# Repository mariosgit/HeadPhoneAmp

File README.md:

# HeadPhoneAmp

New plan... Make my own HP Amp.

##### Requirements:

* EQ - I dont have many HP's which I don't want to EQ, they all need a little something.
* Lipo Powered !
* Line In

##### Goodies

* More Inputs (in that order)
   * USB (Teensy4 can also control DSP, Bluetooth, 16bit is ok for playback)
   * BT (just plug in a module CSR8635?)
   * WLAN (Radio, Subsonic and Ampache protocols for nextcloud music) cry for ESP32 (rabbithole! [bt a2dp](https://github.com/pschatzmann/ESP32-A2DP) [iradio](https://github.com/Edzelf/ESP32Radio-V2) [streem gedoehns](https://github.com/sle118/squeezelite-esp32) )
   * SPDIF (not really on a HP amp)
   * Analog++ Phono MM input with RIAA https://sound-au.com/project06.htm 
* Second output ? With it's own EQ and Volume ?
* NuTube or Simulation of a little distortion. Maybe other effects ?
* MP3 player - there is one for the teensy. Would need SDCard or so, How to copy files ? Just swap the card ? The Cardhold would obscure the VUSB hack !
* ~~Radio streaming.. WLAN hasl...~~

# Status

* Theory is somewhat more defined in my head.
* Started to build some blocks
    * TPA6120 module - Made my own, running with only single 5V - to be tested.
    * DSP - I have a freeDSP-SMD-B to experiment with
    * NuTube ? I have a NuTube HP Amp which is'nt great but could be recycled into something usefull - not so available !

# Tested so far...

## HPAmp Design

TPA6120A2 it's big (there is a QFN version) and a TPS65135 power converter as per datasheet.

After some mangling, it performs well, no noise and quite some punch.

##### Bugs v0.1

* Wrong TPA6120 footprint :-(

##### Bugs v0.2 / Eval

* ~~Oszilation on left output 12MHz ?? goes awai when osziloscoping the input line !?~~ Gone after adding C5, C4 2.2u from se reste kiste.
* There is some noise and DC offset of 500mV, as is in the PRC breakout of this amp. Added 1k @ inputs to ground -> silence, no/minimal Vout offset.
* input resistors to ground ? **YES** !
    * 47k was noisy
    * 1k is ok, depends on input ? consider previous stage power output !
* 10uF caps footprint could be larger / dual 1206?
* On/Off clics ? Not too bad.
* Add TestPoints for L/R inputs
* Add LEDs for +-5V ?
* TestPoint and pullup for EN pin.
* More ground pads.
* Does not work with small BAT/Charger? Toggles on/off

## Power Block Design

* Use Adafruit PowerThing ?
    * Added charge pump for 10V as in the DS
* How to get the teensy integrated, would need to patch into VUSB -> PowerBlock -> 5V back to the Teensy ?
    * Cut trace in the back, solder some wire to VUSB ? Or use pogopins ? Not nice.
* Noise ??? Will see... yes 200mVpp @ 65kHz, audible when directly driving a 16ohm speaker

* Cap Mult for analog voltage, or just a regulator ? [SIM](https://www.falstad.com/circuit/circuitjs.html?ctz=CQAgjCAMB0l3BWcDoBYDsAmdA2dBOdMMADhzEnxAQiVQGZqBTAWmICgAnEbTHkkjyzgwfSMkjsAxuHx8wuWX0ypxa2PEiY+6aPjAMi6dJAOpMCdCDaTuOVOEVgc4hTig9McdgDdr+d20HFgCRMXBweAiqdQR2AHN-QJUk-kE1BKFlASyQekgHDIB3HkhBYmVhCvB2ABclcFQHMDkwvIiWGDl9fEh0BHwEchILMWgcQYQtS3xzPonmuBAAEyYAMwBDAFcAG1r2EpbswV40qAOGt0um88OXR3cjxsKL+weQN+qwV+bRd+rJAAHPIIeQ3eigniqdrFEFghwQ+R-SQlRFtU4Ai5olTibE5FFws6nTD4i4hdwseh8cltAk06qfZEXJ6oE7CVnnGRPSnyVoc9SaLR8EjQYxgBAIVT0QgUVA4QQ2TIs8qtN4ZbinDmnHkecVAwk6tEcxiwo1svj8smhHVsClU24NHXa+3fErOvhonW2azOawu1pemqHVoklXKaGSAD27XSIAAHiQTGAAEYfKAaUy6njWdD0djRsCMWMJ-J-eh6HDkBACPDEaX0dwweAQFvZli4fPgIseONSQt-CjpiDyCIwJBRqEgYt90zydQQRitsfnejlEAAMQgAs0W4zFAgbBAAGENoCNlIAJa1DYAOykTHYq48m6z+59IAASkwAM4X7-Xu8HyAA)

##### Results v0.1

* C6 can be much larger according to DS. Available up to 220uF.
* Has no BAT protection ? The testbat emptied down to 2V ! Just clarify.
* Make charge Amps quick changeable with a PHT resistor ?
* Could add a PG PowerGood LED, this shows when device is connected to some power source
* Check 10V load ❗
* Add option for higher voltage as in the GP??94 controller ?

##### Bugs v0.1

* ! Q1 (low bat indicator) is **wrong** MMUN2133LT1G it's BEC(123) - just switched to the "BEC" symbol. ✅
* C5 (+10V) was connected to ground, should be between +10 and +5V, works anyway ✅
* Can it provide 50V using a longer charge pump ?

# Next up ?

## NuTube

* Create own board 
    * Bias voltage driven by OpAmp ! Input a single Pot or CV
    * With ADC ? as a FX loopback ?
* Loop back Nutube to DSP ? With an extra ADC or CODEC ? Ad

## VFD/OLED

* Make board for MN12832 ?
    * Can I borrow voltage from the power block ? Add more charge pumps..

## Teensy/ESP32/STM32 + DSP

* Can the teensy be slave i2s ??? Otherwise it would need an extra SRC.
    There is a slave i2s out... Will it work with usb, does it need to be 44100kHz ?
    ```
    AudioInputUSB            usb1;
    AudioOutputI2Sslave      i2sslave1;
    AudioConnection          patchCord1(usb1, 0, i2sslave1, 0);
    AudioConnection          patchCord2(usb1, 1, i2sslave1, 1);
    ```
    ```File > Examples > Audio > HardwareTesting > WM8731MikroSine```
    *Notes: Slave mode I2S should not used in the same project as ADC, DAC and PWM signals. Differences in timing between the I2S device and Teensy's clock can cause occasional audio glitches when I2S slave mode is used together with other input or output objects based on Teensy's timing. ...Only one I2S input and one I2S output object may be used. Master and slave modes may not be mixed (both must be of the same type).*
    Mhm wanted to use the internal DAC for NuTube bias...
* Test I2S slave (with DSP)
* Test internal DAC for NuTube

## BT Audio

* Ahh just another SRC needed ??? Or switch them between Teensy and BT ? And SPDif ?
* Make a SPDIF/BT/USB I2S Switch + SRC  block design. it's all there.

## SRC Board

Because PRC boards are somewhat lacking...

* Jumpers/DIP-Switches for config !

## ADC Board ? 

For more channels ? or FX loops
* PCM1808 1.2Eur - 99db somewhat outdated, TI says try the PCM1822 ! ~3 Eur

## Analog mess

### BBE

### uPC1892

# Log

| What | Time | Cost || What | Time | Cost |
|---|---|---|---|---|---|---|
| Make Power PCB | 1d | | | Test,Fix Power PCB | 1d | |
|  Make HPBooster PCB | 1d | | | | | |
| both mat+pcb | | 50 + 30 | | |

# Refs

Used some Symbols... https://github.com/wykys/klib 

Ti's [I2C expander collection](https://www.ti.com/interface/i2c/general-purpose-ios-gpios/overview.html?keyMatch=i/o%20expander&tisearch=search-everything)

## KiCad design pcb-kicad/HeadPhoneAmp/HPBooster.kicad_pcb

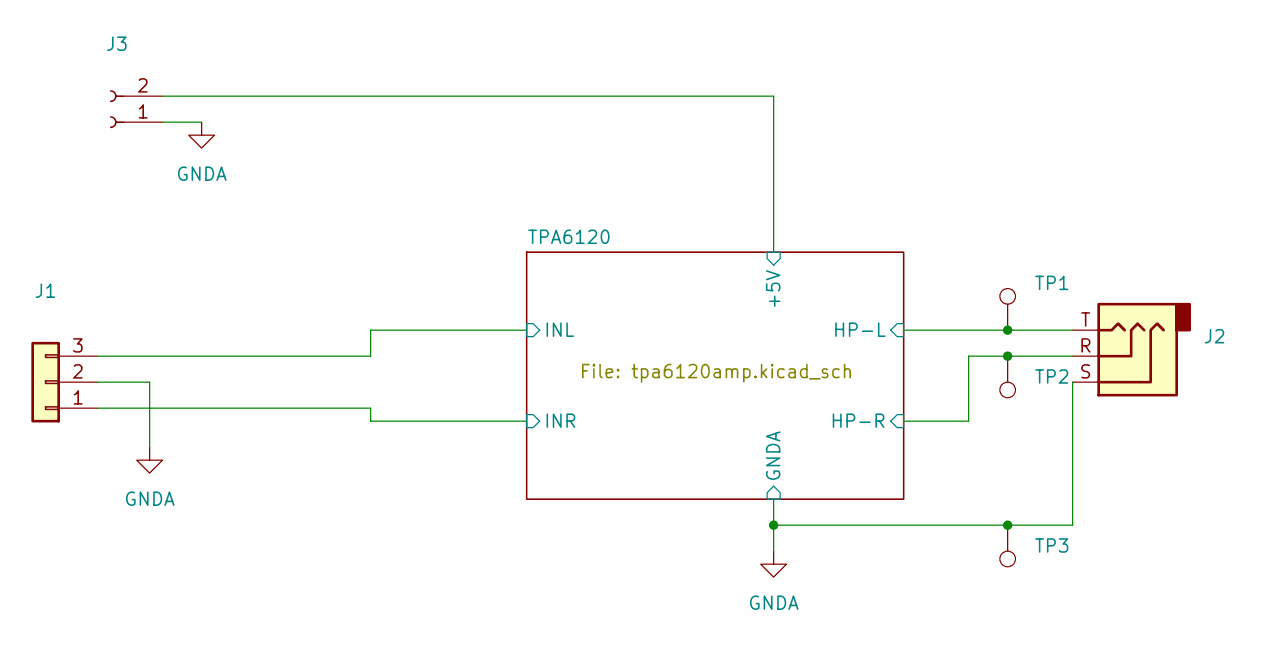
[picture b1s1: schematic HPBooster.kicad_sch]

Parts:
J1: JST_EH_B3B-EH-A_1x03_P2.50mm_Vertical
J2: Jack_3.5mm_CUI_SJ-3523-SMT_Horizontal
J3: PinHeader_1x02_P2.54mm_Vertical
TP1, TP2, TP3: TestPoint_Loop_D1.80mm_Drill1.0mm_Beaded

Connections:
+5V: J3.2; also elsewhere on the board
/TPA6120/HP-L: J2.T, TP1.1; also elsewhere on the board
/TPA6120/HP-R: J2.R, TP2.1; also elsewhere on the board
/TPA6120/INL: J1.3; also elsewhere on the board
/TPA6120/INR: J1.1; also elsewhere on the board
GNDA: J1.2, J2.S, J3.1, TP3.1; also elsewhere on the board

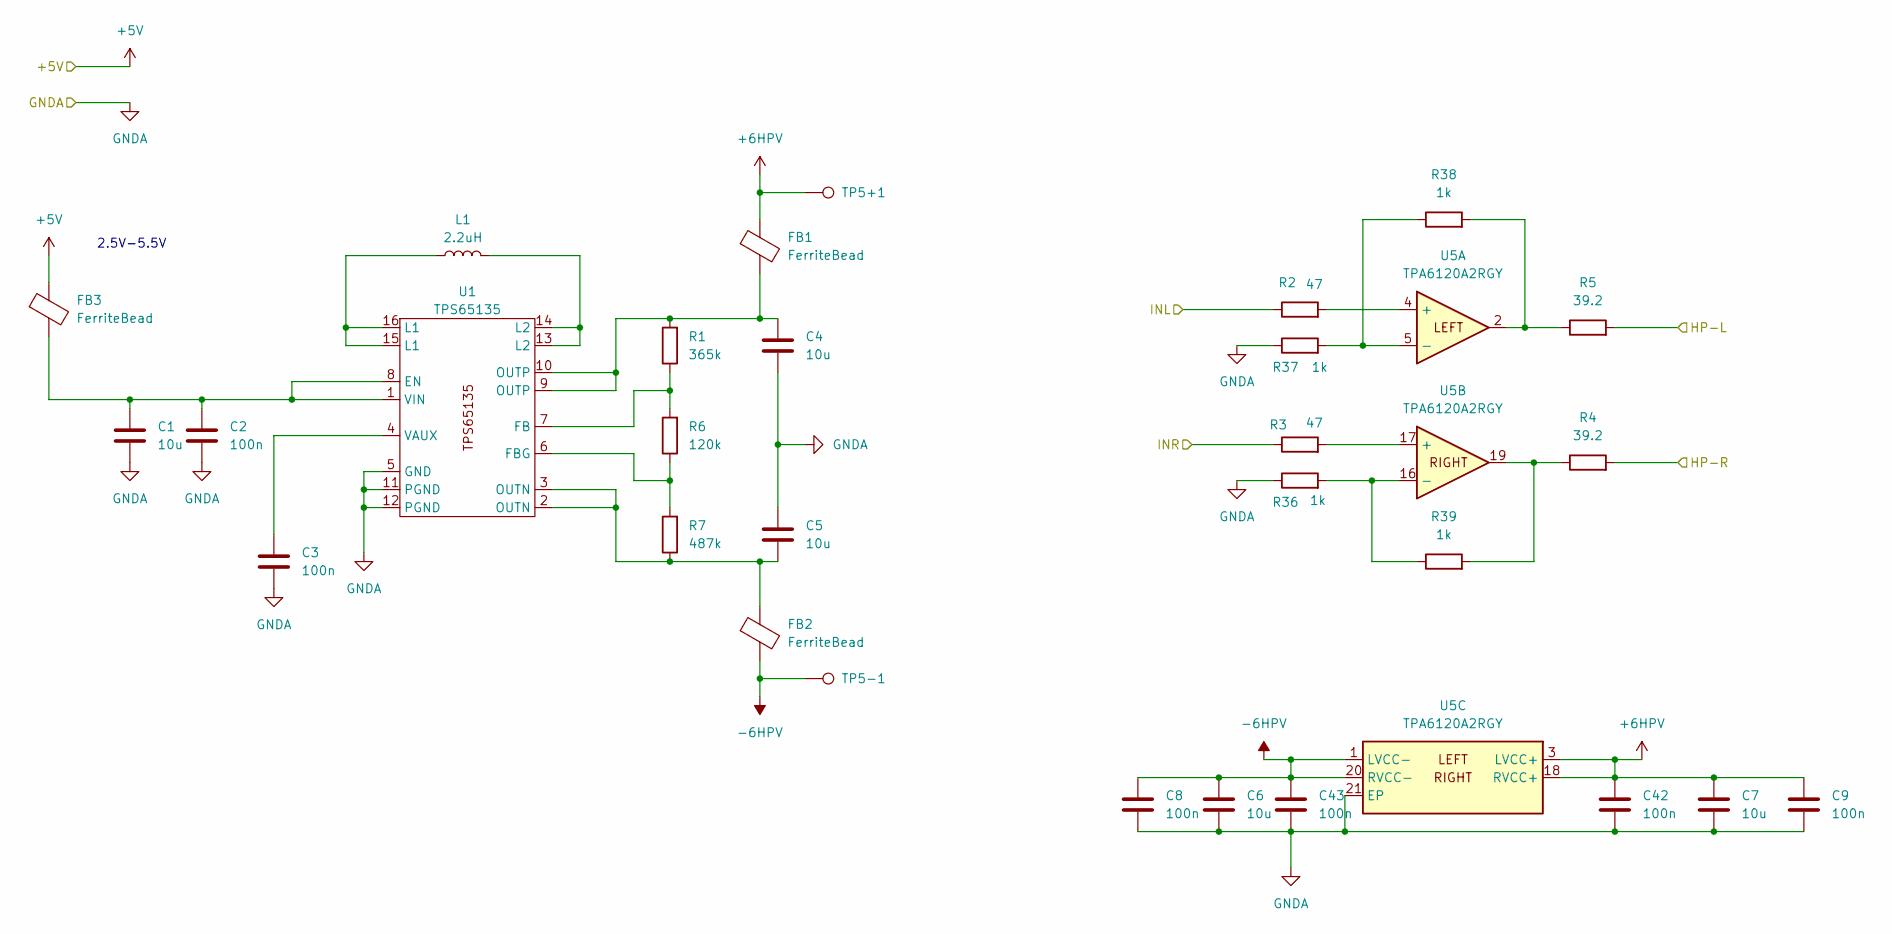
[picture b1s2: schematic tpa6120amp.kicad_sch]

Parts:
C1, C4, C5, C6, C7: 10u; C_0603_1608Metric_Pad1.08x0.95mm_HandSolder
C2, C3, C8, C9, C42, C43: 100n; C_0603_1608Metric_Pad1.08x0.95mm_HandSolder
FB1, FB2, FB3: FerriteBead; L_0603_1608Metric_Pad1.05x0.95mm_HandSolder
L1: 2.2uH; L_1812_4532Metric_Pad1.30x3.40mm_HandSolder
R1: 365k; R_0603_1608Metric_Pad0.98x0.95mm_HandSolder
R2, R3: 47; R_0603_1608Metric_Pad0.98x0.95mm_HandSolder
R4, R5: 39.2; R_2512_6332Metric_Pad1.40x3.35mm_HandSolder
R6: 120k; R_0603_1608Metric_Pad0.98x0.95mm_HandSolder
R7: 487k; R_0603_1608Metric_Pad0.98x0.95mm_HandSolder
R36, R37, R38, R39: 1k; R_0603_1608Metric_Pad0.98x0.95mm_HandSolder
TP5+1, TP5-1: TestPoint_Pad_2.0x2.0mm
U1: TPS65135; WQFN-16-1EP_3x3mm_P0.5mm_LongPad_ThermalVia
U5: TPA6120A2RGY; SOP-20_7.5x12.8mm_P1.27mm

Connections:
+5V: FB3.1; also elsewhere on the board
+6HPV: C7.1, C9.1, C42.1, FB1.1, TP5+1.1, U5.3 (LVCC+), U5.18 (RVCC+)
-6HPV: C6.1, C8.1, C43.1, FB2.2, TP5-1.1, U5.1 (LVCC-), U5.20 (RVCC-)
/TPA6120/HP-L: R5.2; also elsewhere on the board
/TPA6120/HP-R: R4.2; also elsewhere on the board
/TPA6120/INL: R2.1; also elsewhere on the board
/TPA6120/INR: R3.1; also elsewhere on the board
GNDA: C1.2, C2.2, C3.2, C4.2, C5.1, C6.2, C7.2, C8.2, C9.2, C42.2, C43.2, R36.1, R37.1, U1.5 (GND), U1.11 (PGND), U1.12 (PGND), U5.21 (EP); also elsewhere on the board
unnamed: C4.1, FB1.2, R1.2, U1.9 (OUTP), U1.10 (OUTP)
unnamed: C5.2, FB2.1, R7.1, U1.2 (OUTN), U1.3 (OUTN)
unnamed: L1.1, U1.15 (L1), U1.16 (L1)
unnamed: L1.2, U1.13 (L2), U1.14 (L2)
unnamed: R5.1, R38.2, U5.2
unnamed: R4.1, R39.2, U5.19
unnamed: C1.1, C2.1, FB3.2, U1.1 (VIN), U1.8 (EN)
unnamed: R1.1, R6.2, U1.7 (FB)
unnamed: R6.1, R7.2, U1.6 (FBG)
unnamed: C3.1, U1.4 (VAUX)
unnamed: R2.2, U5.4 (+)
unnamed: R37.2, R38.1, U5.5 (-)
unnamed: R3.2, U5.17 (+)
unnamed: R36.2, R39.1, U5.16 (-)

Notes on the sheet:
2.5V-5.5V

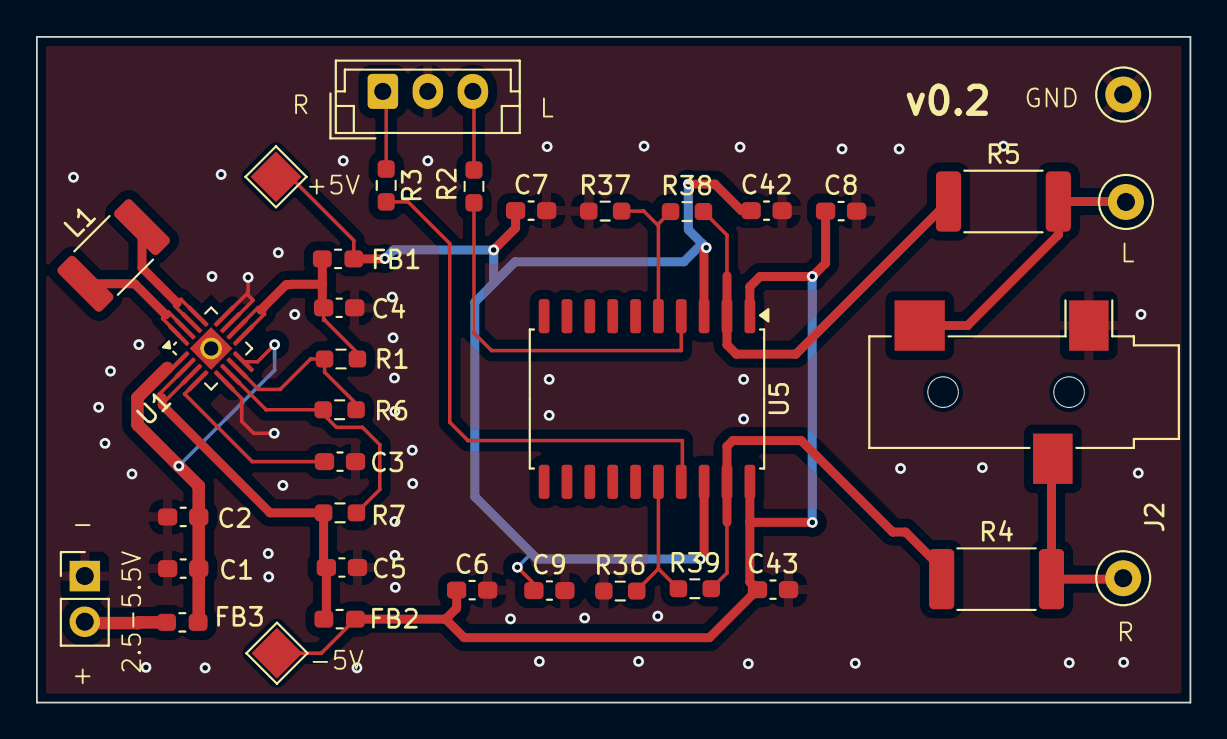
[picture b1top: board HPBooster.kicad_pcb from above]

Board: 2 copper layers, 64.1 x 37.0 mm, 36 parts (0 on the bottom side), 22 nets.

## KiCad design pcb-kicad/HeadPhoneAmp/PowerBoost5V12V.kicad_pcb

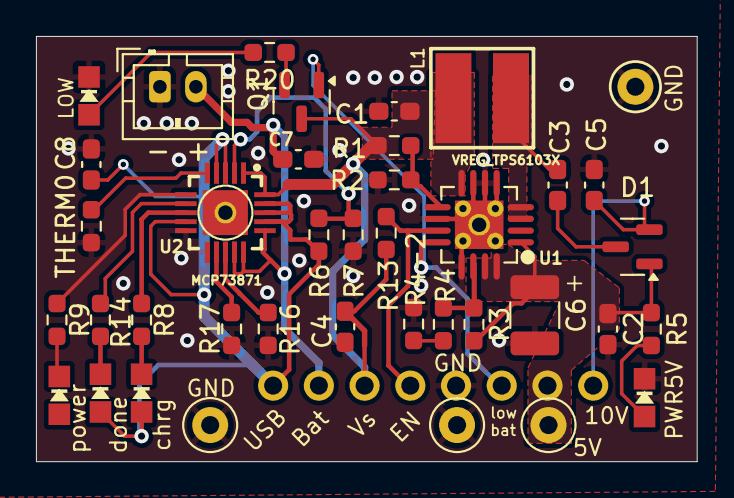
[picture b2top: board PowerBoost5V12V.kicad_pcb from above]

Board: 2 copper layers, 36.7 x 23.6 mm, 41 parts (0 on the bottom side), 26 nets.

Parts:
B1: JST_PH_B2B-PH-K_1x02_P2.00mm_Vertical
C1, C2, C5, C7, C8: 2.2u; C_0603_1608Metric_Pad1.08x0.95mm_HandSolder
C3, C4: 100n; C_0603_1608Metric_Pad1.08x0.95mm_HandSolder
C6: 22u; C_1210_3225Metric_Pad1.33x2.70mm_HandSolder
CHRG/LBO0: CHIPLED_0805_NOOUTLINE
D1: BAT54S; SOT-23
DONE0: CHIPLED_0805_NOOUTLINE
JP2: 1X08_ROUND
L1: 6.8uH 2A; INDUCTOR_5X5MM_TDK_VLC5045
LED1, LED2: CHIPLED_0805_NOOUTLINE
LEDPG1: PG; CHIPLED_0805_NOOUTLINE
Q1: Q_PNP_BEC_BRT; SOT-23
R1, R3: 1.87M; R_0603_1608Metric_Pad0.98x0.95mm_HandSolder
R2: 340k; R_0603_1608Metric_Pad0.98x0.95mm_HandSolder
R4, R4-2, R7, R13, R17: 100k; R_0603_1608Metric_Pad0.98x0.95mm_HandSolder
R5, R8, R9, R14, R16, R20: 1k; R_0603_1608Metric_Pad0.98x0.95mm_HandSolder
R6: 270k; R_0603_1608Metric_Pad0.98x0.95mm_HandSolder
THERM0: 15k; R_0603_1608Metric_Pad0.98x0.95mm_HandSolder
TP1: TestPoint_Keystone_5000-5004_Miniature
TP2, TP3, TP4, TP5: TestPoint_Loop_D1.80mm_Drill1.0mm_Beaded
U1: VREG_TPS6103X; PVQFN-16
U2: MCP73871; QFN20_4MM

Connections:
5.0V: C2.1, C6.1, D1.1 (A), JP2.7, R3.2, R5.1, TP2.1, U1.1 (VOUT), U1.15 (VOUT), U1.16 (VOUT)
+10V: C5.1, D1.2 (K), JP2.8
/ENABLE: JP2.4, R13.2, U1.11 (EN)
/LBO: JP2.6, Q1.1 (B), U1.12 (LBO)
GND: B1.1 (-), C1.2, C2.2, C4.2, C5.2, C6.2, C7.2, C8.2, JP2.5, LED1.C, LED2.C, R2.1, R4-2.1, R7.2, R16.1, R17.1, THERM0.1, TP1.1, TP3.1, TP4.1, TP5.1, U1.5 (PGND), U1.6 (PGND), U1.7 (PGND), U1.10 (SYNC), U1.13 (GND), U1.P$18 (PGND), U1.P$19 (PGND), U1.P$20 (PGND), U1.P$21 (PGND), U1.P$22 (PGND), U1.THERMAL (PGND), U2.P$10 (VSS1), U2.P$11 (VSS2), U2.P$21 (THERMAL)
unnamed: CHRG/LBO0.C, R8.2
unnamed: C3.1, D1.3 (COM)
unnamed: DONE0.C, R14.2
unnamed: C3.2, L1.P$2 (2), U1.3 (SW), U1.4 (SW)
unnamed: LED1.A, R20.1
unnamed: LED2.A, R5.2
unnamed: LEDPG1.C, R9.2
unnamed: Q1.2 (E), R20.2
unnamed: R4.1, R4-2.2
unnamed: R3.1, R4.2, U1.14 (FB)
unnamed: R1.1, R2.2, U1.9 (LBI)
unnamed: R16.2, U2.P$13 (PROG1)
unnamed: R17.2, U2.P$12 (PROG3)
unnamed: R8.1, U2.P$8 (STAT1/LBO)
unnamed: R14.1, U2.P$7 (STAT2)
unnamed: THERM0.2, U2.P$5 (THERM)
unnamed: R6.1, R7.1, U2.P$2 (VPCC)
unnamed: R9.1, U2.P$6 (/PG)
VBAT: C1.1, C4.1, JP2.3, L1.P$1 (1), Q1.3 (C), R1.2, R13.1, U1.8 (VBAT), U2.P$1 (VOUT1), U2.P$20 (VOUT2)
VBUS: C8.1, CHRG/LBO0.A, DONE0.A, JP2.1, LEDPG1.A, R6.2, U2.P$3 (SEL), U2.P$4 (PROG2), U2.P$9 (/TE), U2.P$17 (CE), U2.P$18 (VIN1), U2.P$19 (VIN2)
VLIPO: B1.2 (+), C7.1, JP2.2, U2.P$14 (VBAT1), U2.P$15 (VBAT2), U2.P$16 (VBATSENS)

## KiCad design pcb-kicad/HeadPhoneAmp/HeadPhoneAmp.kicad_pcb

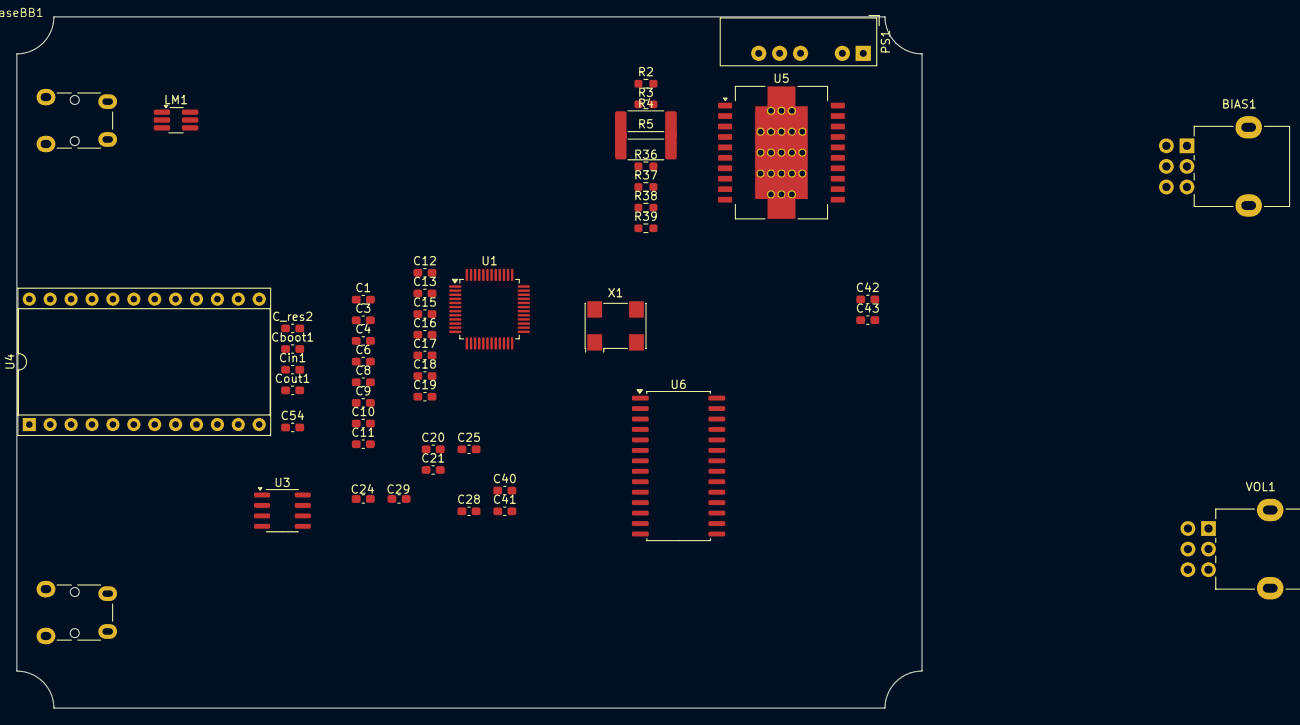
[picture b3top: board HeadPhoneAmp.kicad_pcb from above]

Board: 2 copper layers, 110.0 x 84.0 mm, 51 parts (0 on the bottom side), 33 nets, no tracks yet.

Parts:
BIAS1: R_Potentiometer_Dual; Potentiometer_Alpha_RD902F-40-00D_Dual_Vertical
C1, C3, C4, C6, C8, C9, C10, C11, C13, C16, C17, C40, C41, C42, C43: 100n; C_0603_1608Metric_Pad1.08x0.95mm_HandSolder
C12, C15, C54: 10u; C_0603_1608Metric_Pad1.08x0.95mm_HandSolder
C18: 3n3; C_0603_1608Metric_Pad1.08x0.95mm_HandSolder
C19: 56n; C_0603_1608Metric_Pad1.08x0.95mm_HandSolder
C20, C21: 100p; C_0603_1608Metric_Pad1.08x0.95mm_HandSolder
C24, C25: 330p; C_0603_1608Metric_Pad1.08x0.95mm_HandSolder
C28, C29: 5.6n; C_0603_1608Metric_Pad1.08x0.95mm_HandSolder
C_res2: x; C_0603_1608Metric_Pad1.08x0.95mm_HandSolder
CaseBB1: CaseBB
Cboot1: 220n; C_0603_1608Metric_Pad1.08x0.95mm_HandSolder
Cin1: 2u2; C_0603_1608Metric_Pad1.08x0.95mm_HandSolder
Cout1: 47u; C_0603_1608Metric_Pad1.08x0.95mm_HandSolder
J4, J5: AudioJack3; Jack_3.5mm_Lumberg_1503_07_Horizontal
LM1: LM284x; TSOT-23-6_HandSoldering
PS1: IA0509S; Converter_DCDC_XP_POWER-IAxxxxS_THT
R2, R3: 47; R_0603_1608Metric_Pad0.98x0.95mm_HandSolder
R4, R5: 39.2; R_2512_6332Metric_Pad1.40x3.35mm_HandSolder
R36, R37, R38, R39: 1k; R_0603_1608Metric_Pad0.98x0.95mm_HandSolder
U1: ADAU1701; LQFP-48_7x7mm_P0.5mm
U3: LME49721; SOIC-8_3.9x4.9mm_P1.27mm
U4: DIP-24_W15.24mm_Socket
U5: TPA6120A2RGY; HSOP-20-1EP_11.0x15.9mm_P1.27mm_SlugDown_ThermalVias
U6: PGA4311; SOIC-28W_7.5x17.9mm_P1.27mm
VOL1: R_Potentiometer_Dual; Potentiometer_Alpha_RD902F-40-00D_Dual_Vertical
X1: ASV-24.576MHz-EJ-T; Oscillator_SMD_Abracon_ASV-4Pin_7.0x5.1mm

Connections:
+3V3: C6.2, C8.2, C9.2, C10.2, C11.2, C18.1, C40.1, C41.1, C_res2.1, Cout1.1, U1.6 (SELFBOOT), U1.18 (IOVDD), U1.34 (PVDD), U1.36 (AVDD), U1.38 (PLL_MODE0), U1.39 (PLL_MODE1), U1.48 (AVDD), U3.8 (V+)
+9V: C42.1, PS1.6 (+Vout), U5.3 (LVCC+), U5.18 (RVCC+)
-9V: C43.1, PS1.4 (-Vout), U5.1 (LVCC-), U5.20 (RVCC-)
/HP-AMP/HP-L: J4.T, R5.2
/HP-AMP/HP-R: J4.R, R4.2
/HP-AMP/INL: R2.1, U6.5 (Aout_1)
/HP-AMP/INR: R3.1, U6.24 (Aout_2)
ADC0: J5.R, U1.2 (ADC0)
ADC1: J5.T, U1.4 (ADC1)
BRD_RST: C1.1, U1.5 (~RESET)
GND: C1.2, C3.1, C4.1, C6.1, C8.1, C9.1, C10.1, C11.1, C12.1, C13.2, C15.1, C16.2, C17.2, C20.2, C21.2, C28.2, C29.2, C40.2, C41.2, C54.2, C_res2.2, Cin1.2, Cout1.2, LM1.2 (GND), U1.1 (AGND), U1.7 (ADDR0), U1.12 (DGND), U1.25 (DGND), U1.30 (RSVD), U1.33 (PGND), U1.37 (AGND), U1.42 (AGND), U3.4 (V-), X1.2 (GND)
GNDA: C42.2, C43.2, J4.S, J5.S, PS1.5 (0V), R36.1, R37.1, U5.21 (EP), U6.2 (AGND_1), U6.4 (AGND_1), U6.9 (AGND_3), U6.11 (AGND_3), U6.18 (AGND_4), U6.20 (AGND_4), U6.25 (AGND_2), U6.27 (AGND_2)
unnamed: Cboot1.1, LM1.6 (SW)
unnamed: Cboot1.2, LM1.1 (CB)
unnamed: Cin1.1, LM1.4 (SHDN), LM1.5 (Vin)
unnamed: C3.2, C4.2, U1.13 (DVDD), U1.24 (DVDD)
unnamed: R5.1, R38.2, U5.2
unnamed: R4.1, R39.2, U5.19
unnamed: C16.1, U1.40 (CM)
unnamed: C12.2, C13.1, U1.47 (FILTA)
unnamed: C15.2, C17.1, U1.41 (FILTD)
unnamed: C18.2, C19.2, U1.35 (PLL_LF)
unnamed: C20.1, U3.3 (+)
unnamed: C24.1, U3.1, U3.2 (-)
unnamed: C21.1, U3.5 (+)
unnamed: C25.1, U3.6 (-), U3.7
unnamed: R2.2, U5.4 (+)
unnamed: R37.2, R38.1, U5.5 (-)
unnamed: R3.2, U5.17 (+)
unnamed: R36.2, R39.1, U5.16 (-)
unnamed: U6.7 (VA+), U6.22 (VA+)
unnamed: U6.6 (VA-), U6.23 (VA-)
unnamed: C54.1, X1.1 (Control), X1.4 (Vcc)

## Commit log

2019-09-17 Idea collection.
2019-09-18 Added links.
2019-09-18 More README..
2019-09-18 More text...
2019-09-18 More Links and Style
2019-09-18 Fix ?
2019-09-18 Or sooo?
2019-09-18 Idea Explosion..
2019-09-18 working on it...
2019-09-18 Experimenting... No luck with the ATTiny so far.
2019-09-18 At least tested the display and volume pot on an Arduino
2019-09-18 More theory
2024-07-03 Reconceptionation.
2024-07-09 Added TPA6120 breakout.
2024-07-10 Plan B writeup.
2024-07-11 Added Bat Charger ala PowerBoost.
2024-07-15 Added some order infos.
2024-07-16 Mini fixes
2024-07-18 Fixed PowerBlock PCB it's v0.2 now
2024-07-25 HPBooster v0.2, changed TPA footprint.
2024-07-29 README++
2024-08-03 Eval of v0.2 results.
2024-08-04 nix..
2024-08-05 restructured..
2024-08-05 Clean up.
2024-08-05 more ideas
2024-09-02 nix2
